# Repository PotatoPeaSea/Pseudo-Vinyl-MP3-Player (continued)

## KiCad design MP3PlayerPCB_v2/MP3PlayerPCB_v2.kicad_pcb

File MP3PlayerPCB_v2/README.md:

# MP3PlayerPCB v2: ESP32-CAM main board

v2 is a separate KiCad project. The v1 project in `../MP3PlayerPCB/` is left untouched.

| Top | Bottom |
|---|---|
|  |  |

## What's on the board

| Ref | Part | Notes |
|---|---|---|
| U1 | AI-Thinker ESP32-CAM | Soldered straight in on the standard 2.5 mm header spacer. **Remove the OV2640 camera**: it isn't used, and there's no room for it under the display. |
| U3 | PCF8574TS (SSOP-20), I2C 0x20 | Reads all six inputs. Polled; INT is unused. |
| U2 | AP2112K-3.3 | 600 mA LDO from the battery rail |
| J1 | GC9A01 1.28" round TFT | The display's 7 pins solder straight into the board. Pin names are on the **back** silkscreen. |
| SW1 / SW2 | 6x6 tact, 13 mm actuator | NEXT / PREV, under the lid button holes |
| SW3 | Alps EC11E encoder with switch, H20 | Volume / scroll; push = play/pause |
| SW4 | C&K OS102011MA1Q right-angle slide | Power. The lever pokes through the back wall. |
| SW5 | KMR2 tact | BOOT (pulls IO0 low) |
| J2 | 2-pin wire pads | From the TP4056 Type-C module's OUT+/OUT- (the module stays off-board, as in the CAD, because the case's USB-C hole is at its height) |
| J3 | 1x4 header | PROG: GND / TX(IO1) / RX(IO3) / IO0 |
| J4 | 1x4 header | Spare expander pins P5-P7 + GND (for example a third button) |

## Pin map (ESP32-CAM)

| GPIO | Use |
|---|---|
| 2 / 14 / 15 | Onboard microSD, SDMMC 1-bit (D0 / CLK / CMD). Not routed on this board. |
| 13 | TFT SCLK |
| 12 | TFT MOSI (strapping pin: nothing may pull it high at reset) |
| 0 | TFT DC + BOOT button, 10k pull-up |
| 3 (U0R) | I2C SDA, 4.7k pull-up |
| 1 (U0T) | I2C SCL, 4.7k pull-up |
| 4 | Unused (drives the module's flash LED) |
| 16 | Unused (PSRAM CS) |

TFT CS is tied low. TFT RST is a 10k/1uF power-on reset.

PCF8574: P0 ENC_A, P1 ENC_B, P2 ENC_SW, P3 NEXT, P4 PREV, P5-P7 to J4.

**Flashing:** hold BOOT, switch power off and on, then upload through J3 with a 3.3 V USB-UART adapter (its TX goes to RX). The I2C bus shares those two pins, so the serial debug console isn't available while running.

## Verification (KiCad 10.0.5)

- **ERC:** 0 errors. One warning: the PCF8574TS symbol differs from the KiCad 10 library copy.
- **DRC:** 0 errors, 0 unconnected, 0 schematic-parity issues. 16 warnings: the stock footprints came from the KiCad 7 library. *Update Footprints from Library* clears them.
- 2-layer, 1.6 mm board, 68.4 x 38.5 mm. 0.2 mm clearance, 0.25 mm signals, 0.3 mm 3V3, 0.4 mm battery rail. GND pours on both layers, with a copper keep-out under the ESP32 antenna.

## Fit against `CAD/Music Player Assembly`

The outline is the enclosure cavity minus 0.4 mm. The board's bottom face sits on the battery (z = -3.0 in the assembly frame).

Changes the enclosure needs:

1. Remove the encoder pedestal and the right-hand support block. Both were for the old module layout and now overlap the board.
2. Raise the back-wall power-switch slot by about 2 mm.
3. The display has about 0 mm of clearance over the ESP32 shield. Raise it about 1 mm, or order a 1.0 mm board.
4. Optionally add bosses for M2 holes H1 and H2.

Other things to check before ordering:

- Confirm the ESP32-CAM 3V3/5V row and the display header pin order against your actual parts.
- Trim the ESP32 header pins flush and insulate the board's underside from the LiPo.

`3d/*_placed.stpZ` are your ESP32-CAM and display models with their placement baked in.

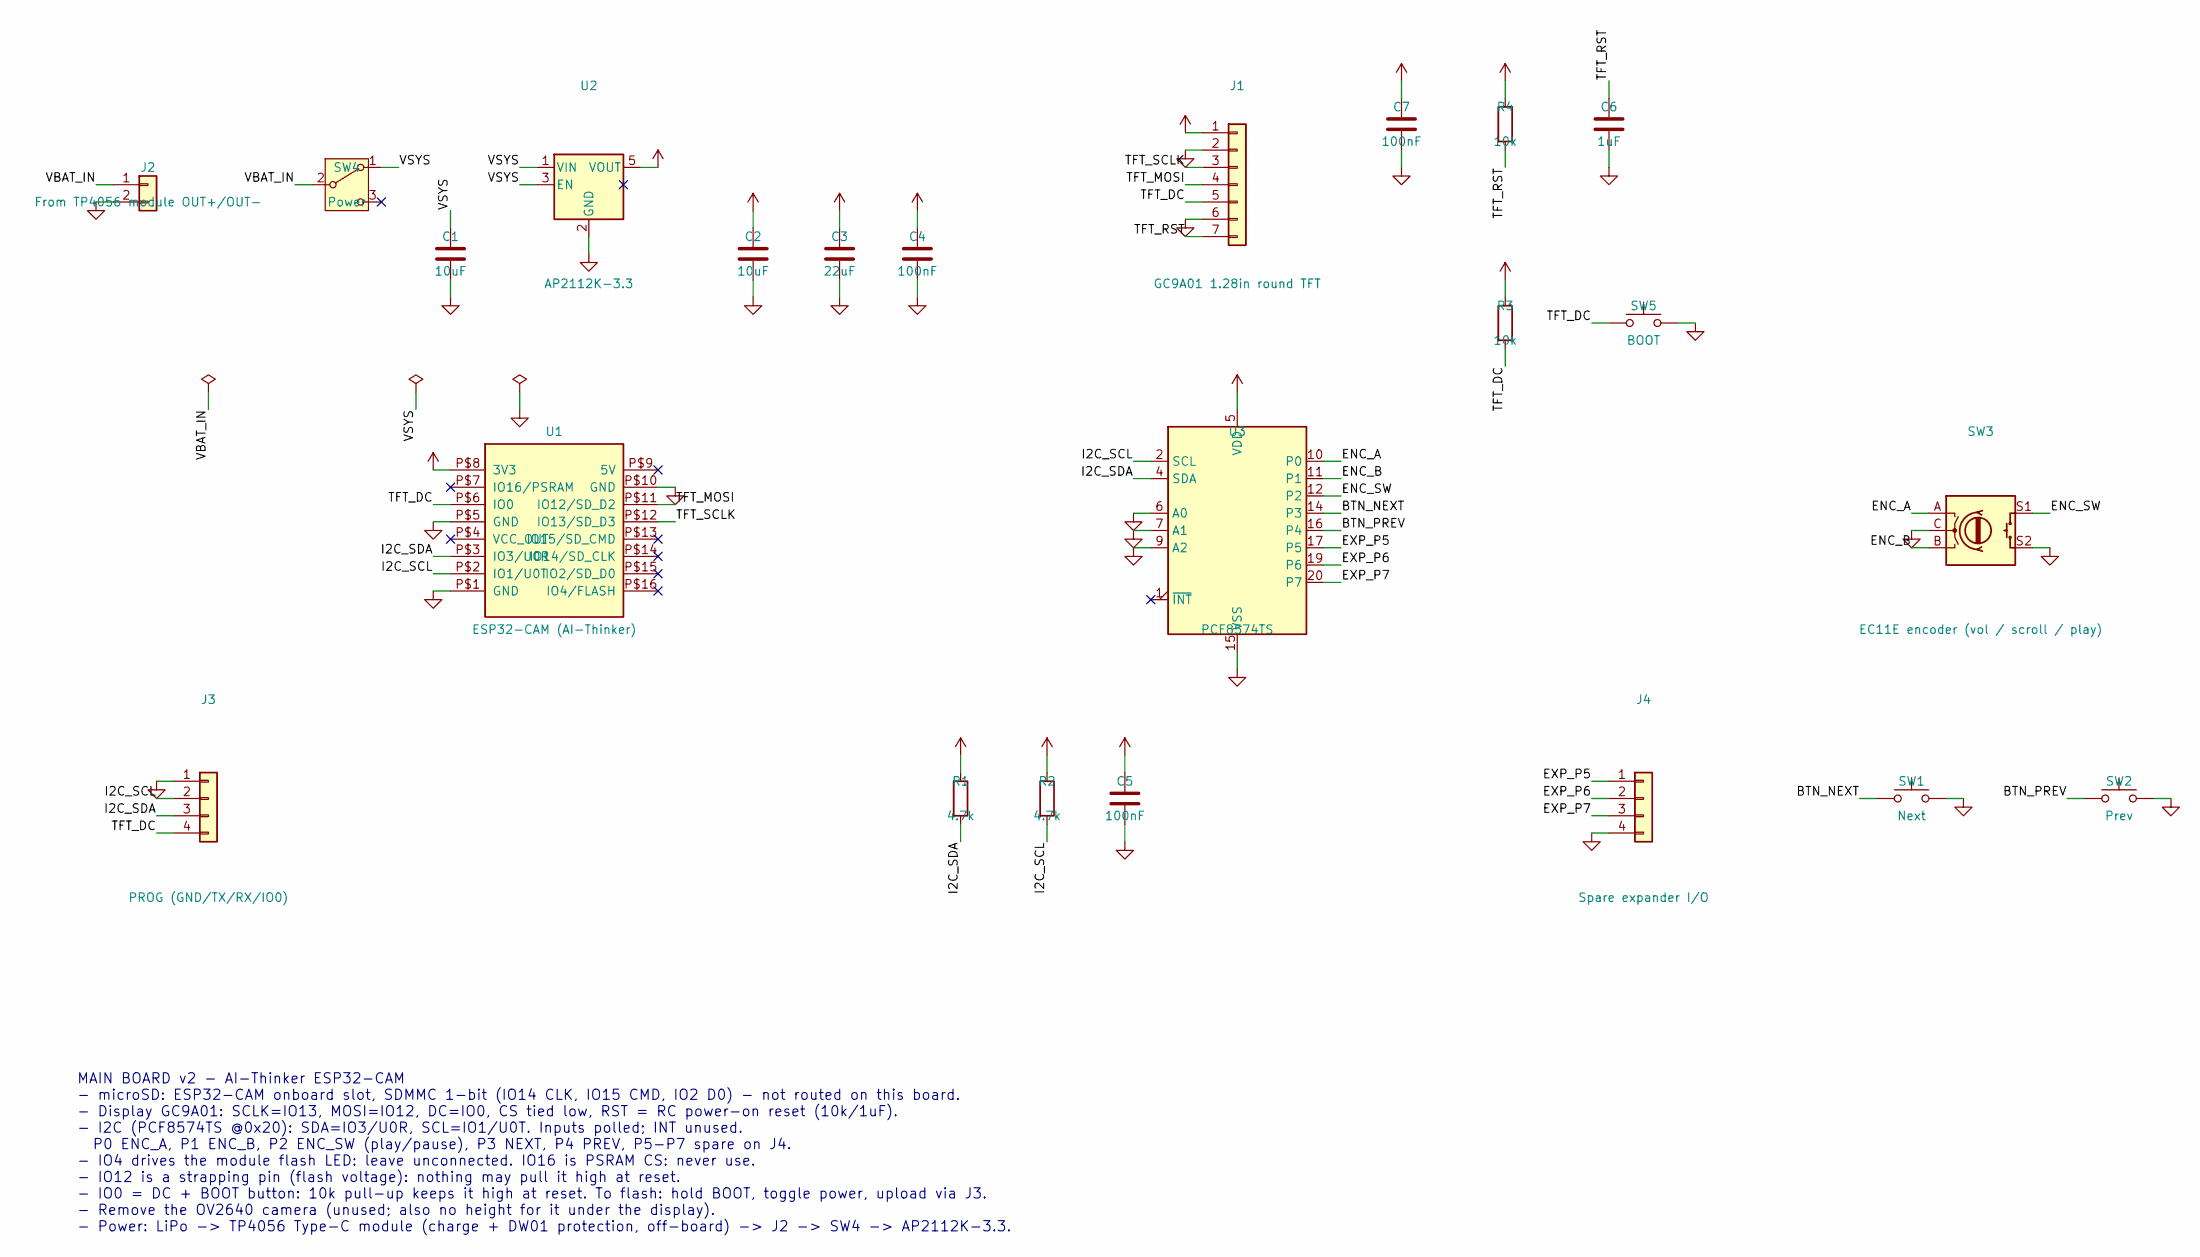
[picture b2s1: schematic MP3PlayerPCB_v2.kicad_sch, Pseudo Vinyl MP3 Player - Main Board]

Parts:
C1, C2: 10uF; C_0805_2012Metric_Pad1.18x1.45mm_HandSolder
C3: 22uF; C_1206_3216Metric_Pad1.33x1.80mm_HandSolder
C4, C5, C7: 100nF; C_0805_2012Metric_Pad1.18x1.45mm_HandSolder
C6: 1uF; C_0805_2012Metric_Pad1.18x1.45mm_HandSolder
J1: GC9A01 1.28in round TFT; GC9A01_Header_1x07
J2: From TP4056 module OUT+/OUT-; PinHeader_1x02_P2.54mm_Vertical
J3: PROG (GND/TX/RX/IO0); PinHeader_1x04_P2.54mm_Vertical
J4: Spare expander I/O; PinHeader_1x04_P2.54mm_Vertical
R1, R2: 4.7k; R_0805_2012Metric_Pad1.20x1.40mm_HandSolder
R3, R4: 10k; R_0805_2012Metric_Pad1.20x1.40mm_HandSolder
SW1: Next; SW_PUSH_6mm_H13mm
SW2: Prev; SW_PUSH_6mm_H13mm
SW3: EC11E encoder (vol / scroll / play); RotaryEncoder_Alps_EC11E-Switch_Vertical_H20mm
SW4: Power; SW_Slide_SPDT_Angled_CK_OS102011MA1Q
SW5: BOOT; SW_Push_1P1T_NO_CK_KMR2
U1: ESP32-CAM (AI-Thinker); ESP32-CAM
U2: AP2112K-3.3; SOT-23-5
U3: PCF8574TS; SSOP-20_4.4x6.5mm_P0.65mm

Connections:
+3V3: C2.1, C3.1, C4.1, C5.1, C7.1, J1.1, R1.1, R2.1, R3.1, R4.1, U1.P$8 (3V3), U2.5 (VOUT), U3.5 (VDD)
/BTN_NEXT: SW1.1, U3.14 (P3)
/BTN_PREV: SW2.1, U3.16 (P4)
/ENC_A: SW3.A, U3.10 (P0)
/ENC_B: SW3.B, U3.11 (P1)
/ENC_SW: SW3.S1, U3.12 (P2)
/EXP_P5: J4.1, U3.17 (P5)
/EXP_P6: J4.2, U3.19 (P6)
/EXP_P7: J4.3, U3.20 (P7)
/I2C_SCL: J3.2, R2.2, U1.P$2 (IO1{slash}U0T), U3.2 (SCL)
/I2C_SDA: J3.3, R1.2, U1.P$3 (IO3{slash}U0R), U3.4 (SDA)
/TFT_DC: J1.5, J3.4, R3.2, SW5.1, U1.P$6 (IO0)
/TFT_MOSI: J1.4, U1.P$11 (IO12{slash}SD_D2)
/TFT_RST: C6.1, J1.7, R4.2
/TFT_SCLK: J1.3, U1.P$12 (IO13{slash}SD_D3)
/VBAT_IN: J2.1, SW4.2 (B)
/VSYS: C1.1, SW4.1 (A), U2.1 (VIN), U2.3 (EN)
GND: C1.2, C2.2, C3.2, C4.2, C5.2, C6.2, C7.2, J1.2, J1.6, J2.2, J3.1, J4.4, SW1.2, SW2.2, SW3.C, SW3.S2, SW5.2, U1.P$1 (GND), U1.P$5 (GND), U1.P$10 (GND), U2.2 (GND), U3.6 (A0), U3.7 (A1), U3.9 (A2), U3.15 (VSS)

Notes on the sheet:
MAIN BOARD v2 - AI-Thinker ESP32-CAM - microSD: ESP32-CAM onboard slot, SDMMC 1-bit (IO14 CLK, IO15 CMD, IO2 D0) - not routed on this board. - Display GC9A01: SCLK=IO13, MOSI=IO12, DC=IO0, CS tied low, RST = RC power-on reset (10k/1uF). - I2C (PCF8574TS @0x20): SDA=IO3/U0R, SCL=IO1/U0T. Inputs poll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

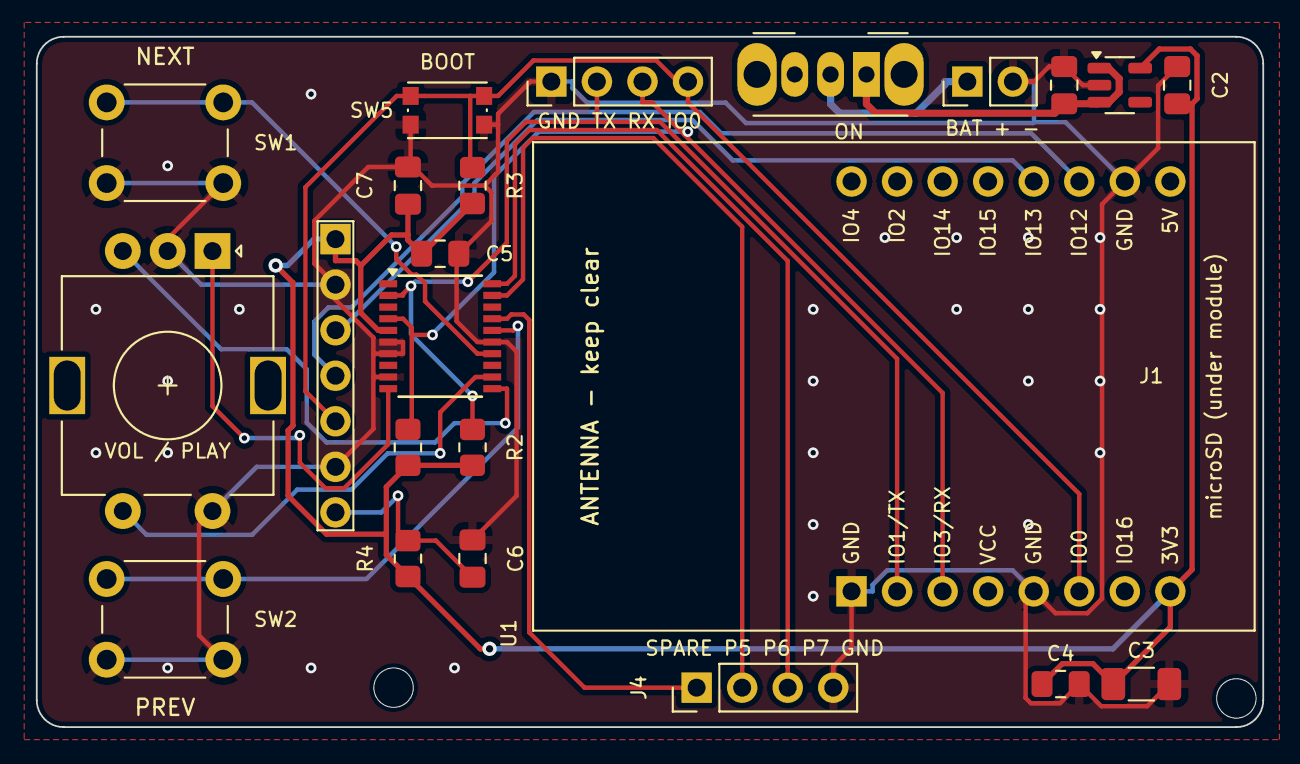
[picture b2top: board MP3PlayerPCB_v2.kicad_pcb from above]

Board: 2 copper layers, 68.4 x 38.5 mm, 25 parts (0 on the bottom side), 18 nets.

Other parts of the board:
H1, H2: M2; MountingHole_2.2mm_M2

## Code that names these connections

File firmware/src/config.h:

#pragma once
/**
 * Pseudo Vinyl MP3 Player — Hardware Configuration
 * Board: ESP32-WROVER N4R8 (classic ESP32, 4MB flash, 8MB PSRAM)
 *
 * Pin rules for this module:
 *  - GPIO 6-11 are flash — never use
 *  - GPIO 16/17 are the PSRAM CS/CLK lines on WROVER — never use.
 *  - GPIO 12 (MTDI) strapping: a pull-up at boot bricks flash voltage —
 *    left unused. No longer at risk from the SD card either: SD moved to
 *    the SDMMC peripheral's 1-bit mode (below), which doesn't touch it.
 *  - GPIO 34/35/36/39 are INPUT-ONLY, no internal pull-ups
 *  - ADC2 pins can't do analogRead while Bluetooth is on → battery on ADC1
 *  - SD card uses the SDMMC peripheral, not SPI — on classic ESP32 its
 *    CLK/CMD/D0-D3 pins are fixed in the IOMUX (not GPIO-matrix routable,
 *    unlike the display's SPI pins below), so GPIO 14/15/2 aren't a free
 *    choice — see the SD Card block.
 *  - GPIO 0 is now unused by this design (it was the display's MOSI pin in
 *    an earlier revision — a boot-strapping pin, moved off deliberately).
 */

// ── Feature Flags ───────────────────────────────────────────
#ifndef BT_ENABLED
#define BT_ENABLED          1
#endif

// Debug run mode: serial console simulates buttons/encoder (no hardware
// needed). Enable by building the esp32dev-debug environment.
#ifndef DEBUG_MODE
#define DEBUG_MODE          0
#endif

// ── Display: GC9A01 (240×240 round IPS) ─────────────────────
// NOTE: pins are duplicated in platformio.ini TFT_eSPI build flags —
// keep both in sync!
//
// Routed through the GPIO matrix (none of these are VSPI/HSPI IOMUX-native
// pins), same as before — see platformio.ini's SPI_FREQUENCY note if the
// panel tears or shows garbage. No strapping-pin caution needed on this
// revision: none of MOSI/SCLK/CS/DC/RST below are boot-strap pins.
#define DISPLAY_WIDTH       240
#define DISPLAY_HEIGHT      240
#define PIN_TFT_MOSI        23      // SDA
#define PIN_TFT_SCLK        19      // SCL
#define PIN_TFT_CS          22
#define PIN_TFT_DC          21
#define PIN_TFT_RST         27
// Display module has no backlight pin (BL hardwired on-board); brightness
// control is unavailable.

// ── SD Card (SDMMC peripheral, 1-bit mode) ──────────────────
// Moved off SPI/HSPI to the ESP32's dedicated SDMMC peripheral (see
// sd_manager.cpp — SD_MMC library, not SD/SPI). On classic ESP32 the
// SDMMC pins are fixed in the IOMUX and NOT GPIO-matrix routable, so
// these three are the only usable values, not a preference:
#define PIN_SD_CLK          14
#define PIN_SD_CMD          15
#define PIN_SD_D0           2
// 1-bit mode only uses the three pins above — D1/D2/D3 (GPIO 4/12/13 on
// this SoC) stay fully free for other use. In particular this is why
// GPIO 12's old strapping caution no longer applies: nothing drives it.

// ── Audio: Bluetooth A2DP only ──────────────────────────────
// Wired I2S/PCM5102 output was removed back on the no-PSRAM WROOM-32: the
// Classic-BT + A2DP stack (~108KB) plus SD/FATFS + LVGL UI left no room for
// a second output path. Output is Bluetooth-only. The WROVER's PSRAM would
// now make a second path affordable, but re-adding it is out of scope here
// and the pins were reclaimed for the rewired display/SD.

// ── Rotary Encoder (KY-040) ─────────────────────────────────
#define PIN_ENC_A           32
#define PIN_ENC_B           33
#define PIN_ENC_SW          5       // moved off 27 — now TFT RST
                                    // (GPIO 5 freed when TFT SCLK moved to 19)

// ── Buttons ─────────────────────────────────────────────────
#define PIN_BTN_PLAY        13
#define PIN_BTN_NEXT        18      // moved off 14 — now SD CLK (SDMMC)
                                    // (GPIO 18 freed when SD moved off SPI)
#define PIN_BTN_PREV        4

// ── Battery voltage divider (ADC1_CH6 — usable with BT on) ──
#define PIN_BATT_ADC        34

// ── Bluetooth ───────────────────────────────────────────────
#define BT_DEVICE_NAME      "Pseudo Vinyl"
// ~58ms of 44.1k stereo PCM. 8KB (46ms) stuttered on hardware; 16KB starved
// the Bluedroid media path (+ resident decoder) and killed the stream
// entirely. 10KB is the compromise — underrun telemetry in the data
// callback measures whether it is enough. Allocated once at boot.
#define BT_RINGBUF_BYTES    (10 * 1024)
// Cap on the discovery list — every entry costs a String on the heap and a
// ~700-byte LVGL button; without a cap a busy radio environment grows it
// unbounded.
#define MAX_BT_DEVICES      8

// ── Audio Defaults ──────────────────────────────────────────
#define DEFAULT_VOLUME      12      // 0-21
#define MAX_VOLUME          21

// ── Library limit ───────────────────────────────────────────
// Hard cap on songs loaded into RAM. Each LVGL list button is ~700 bytes
// (only while the song-list screen is shown); one shared SongInfo vector
// holds the library for the whole app.
#define MAX_SONGS           15

// Playlists = top-level SD folders, plus a synthesized "All Songs" (root)
// entry. Cheap in RAM (two Strings per entry, no song data), capped mainly
// so the Playlists screen's LVGL button list stays bounded like Song List
// and Bluetooth already are.
#define MAX_PLAYLISTS       8

// ── Album Art ───────────────────────────────────────────────
// 240×240 RGB565 (112.5KB) — the display's native resolution, and the
// largest size the pre-scaler tool has ever produced, so no .art file is
// ever rejected on size grounds. The vinyl label still renders at 90px
// (lv_img_set_zoom downscales at display time), so this cap is purely
// about accepting whatever the tool wrote, not a rendering size. Raised
// from 90 on the no-PSRAM WROOM-32: that board's 240×240 buffer (113KB)
// couldn't fit next to the BT stack, but the WROVER's PSRAM absorbs
// allocations this size automatically (anything >4KB lands in PSRAM, see
// docs/MEMORY.md "Board change: WROOM-32 → WROVER N4R8").
#define ART_MAX_SIDE        240
#define ART_MAX_BYTES       (ART_MAX_SIDE * ART_MAX_SIDE * 2)

// ── UI Constants ────────────────────────────────────────────
#define VINYL_SPIN_SPEED_DEG 1       // Degrees per frame — was 2 (120°/s);
                                      // halved because the bigger per-frame
                                      // jump looked jittery even at a
                                      // confirmed 60Hz redraw (LV_DISP_DEF_REFR_PERIOD)
#define UI_REFRESH_MS        16      // ~60fps LVGL tick
#define INPUT_POLL_MS        5       // Button/encoder poll interval
#define DEBOUNCE_MS          50      // Button debounce

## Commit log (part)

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2026-03-04 Initial commit: PRD, README, and project structure
2026-03-05 Add desktop album art pre-scaler tool (prescale_art.py)
2026-03-05 Add GUI album art converter with drag-and-drop and one-click launcher
2026-03-05 Add PyInstaller build support, update gitignore for build artifacts
2026-03-05 Restyle GUI: vintage vinyl theme with wood grain, gold accents, centered header
2026-03-05 Fix: center record sleeve icon in drop zone
2026-03-05 Add complete firmware skeleton: display, audio, input, SD, LVGL UI with vinyl theme
2026-03-06 built firmware, not tested
